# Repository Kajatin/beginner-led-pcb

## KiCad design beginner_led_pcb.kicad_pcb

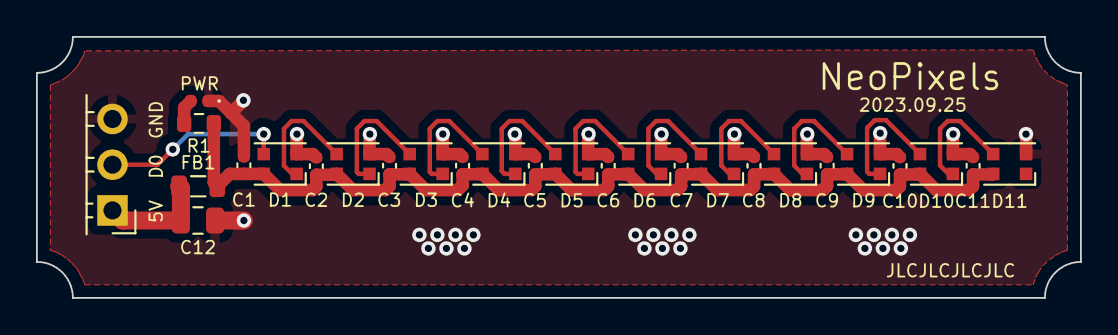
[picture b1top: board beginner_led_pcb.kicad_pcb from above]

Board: 2 copper layers, 58.0 x 14.5 mm, 27 parts (0 on the bottom side), 15 nets.

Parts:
C1, C2, C3, C4, C5, C6, C7, C8, C9, C10, C11: 100n; C_0402_1005Metric
C12: 10u; C_0805_2012Metric
D1, D2, D3, D4, D5, D6, D7, D8, D9, D10, D11: WS2812B; LED_WS2812B-2020_PLCC4_2.0x2.0mm
FB1: FerriteBead_Small; L_0805_2012Metric
J1: Conn_01x03_Pin; PinHeader_1x03_P2.54mm_Horizontal
PWR: LED; LED_0402_1005Metric
R1: 1k0; R_0603_1608Metric

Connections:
+5V: C1.1, C2.1, C3.1, C4.1, C5.1, C6.1, C7.1, C8.1, C9.1, C10.1, C11.1, D1.4 (VDD), D2.4 (VDD), D3.4 (VDD), D4.4 (VDD), D5.4 (VDD), D6.4 (VDD), D7.4 (VDD), D8.4 (VDD), D9.4 (VDD), D10.4 (VDD), D11.4 (VDD), FB1.2, R1.1
D0: D1.3 (DIN), J1.2
GND: C1.2, C2.2, C3.2, C4.2, C5.2, C6.2, C7.2, C8.2, C9.2, C10.2, C11.2, C12.1, D1.2 (VSS), D2.2 (VSS), D3.2 (VSS), D4.2 (VSS), D5.2 (VSS), D6.2 (VSS), D7.2 (VSS), D8.2 (VSS), D9.2 (VSS), D10.2 (VSS), D11.2 (VSS), J1.3, PWR.1 (K)
unnamed: D1.1 (DOUT), D2.3 (DIN)
unnamed: D2.1 (DOUT), D3.3 (DIN)
unnamed: D3.1 (DOUT), D4.3 (DIN)
unnamed: D4.1 (DOUT), D5.3 (DIN)
unnamed: D5.1 (DOUT), D6.3 (DIN)
unnamed: D6.1 (DOUT), D7.3 (DIN)
unnamed: D7.1 (DOUT), D8.3 (DIN)
unnamed: D8.1 (DOUT), D9.3 (DIN)
unnamed: D9.1 (DOUT), D10.3 (DIN)
unnamed: D10.1 (DOUT), D11.3 (DIN)
unnamed: PWR.2 (A), R1.2
unnamed: C12.2, FB1.1, J1.1

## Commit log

2023-09-24 simple led pcb design
2023-09-25 gerber files
2023-09-25 new components
2023-09-26 ignore zip
